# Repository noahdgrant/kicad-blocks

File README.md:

# kicad-blocks

Share schematic sheets across multiple KiCAD projects and reuse their PCB layouts.

`kicad-blocks` is a CLI that lets you treat hierarchical schematic sheets as the source of truth for a section of a board (MCU subsystem, power, etc.) and replay that section's layout across multiple PCB projects. One MCU sheet, many boards — modular dev panels, all-in-one dev boards, space-constrained production boards — without copy-paste or DNP gymnastics.

> Status: pre-alpha. The v0.1 PRD lives at [issue #1](https://github.com/noahdgrant/kicad-blocks/issues/1) and the implementation slices at issues [#2–#13](https://github.com/noahdgrant/kicad-blocks/milestone/1).

## What it does

Given KiCAD projects that share hierarchical schematic sheets (KiCAD 6+ instance-data model), `kicad-blocks` provides four commands:

- **reuse** — copy a sheet's PCB layout (footprint placements, tracks, vias, zones, silkscreen) from a source PCB into a target PCB, anchored at a footprint refdes. Pass `--dry-run` to preview the planned placements without writing.
- **sync** — re-apply after the source layout changes, with a dry-run diff and interactive confirmation.
- **scaffold** — generate a new KiCAD project skeleton wired up to a chosen set of shared sheets.
- **panelize-config** — emit a [KiKit](https://github.com/yaqwsx/KiKit) JSON config to panelize a set of modular PCBs.

After a successful `reuse`, the plugin writes a `<project>.kicad-blocks.lock.json` sidecar next to the config recording the source PCB hash, the applied block hash, the anchor refdes, and the plugin version. **Commit this file to git** — `sync` consults it to detect drift, and shipping it makes diffs reviewable across machines.

Every subcommand also accepts `--format json` for machine-readable output. The JSON envelope is versioned (`schema_version: 1`) and shared by success and failure cases, so a consumer can parse a single stream and branch on the top-level `ok` field. Errors travel as structured entries under `errors[]` on stdout, and exit codes match the default text mode.

## Status

- KiCAD 9 only (uses the modern instance-data schematic model)
- Pure-Python S-expression parsing via [kiutils](https://github.com/mvnmgrx/kiutils)
- MIT licensed

## Install

```sh
pipx install kicad-blocks
```

## Quick start: reuse and sync

Assume you have two KiCAD projects sharing a hierarchical sheet `sheets/mcu.kicad_sch`: a fully-routed `mcu-module/` project that owns the canonical layout, and a `dev-board/` project that wants the same MCU section dropped in.

1. **Scaffold the target project** (skip if you already have one):

   ```sh
   kicad-blocks scaffold --name dev-board --sheets ../sheets/mcu.kicad_sch
   ```

2. **Place the anchor footprint** in `dev-board/dev-board.kicad_pcb` — typically the MCU itself (e.g. `U1`) — at the position and rotation where you want the block to land. Save the board.

3. **Write `dev-board/kicad-blocks.toml`**:

   ```toml
   [[blocks]]
   source   = "../mcu-module/mcu-module.kicad_pcb"
   sheet    = "sheets/mcu.kicad_sch"
   anchor   = "U1"
   ```

4. **Validate the config** before touching the board:

   ```sh
   kicad-blocks validate
   ```

5. **Preview** the planned placement, then apply:

   ```sh
   kicad-blocks reuse --dry-run    # prints the items that would be placed
   kicad-blocks reuse               # writes dev-board.kicad_pcb atomically
   ```

   A `dev-board.kicad-blocks.lock.json` sidecar appears next to your config — commit it.

6. **Later, when the source layout changes**, re-sync:

   ```sh
   kicad-blocks sync --dry-run     # diff: added / removed / moved / net-rewired
   kicad-blocks sync                # prompts before overwriting
   ```

   If `dev-board.kicad_pcb` was hand-edited *inside* the block region since the last apply, `sync` refuses and tells you to pass `--force` once you've reconciled the changes.

For a panel of modular PCBs, declare the `[panelize]` section of `kicad-blocks.toml` and emit a KiKit config with `kicad-blocks panelize-config --out panel.json`, then run KiKit yourself.

## Reporting issues

Bug reports and feature requests welcome at the [issue tracker](https://github.com/noahdgrant/kicad-blocks/issues). Please include the KiCAD version, the `kicad-blocks` version, and a minimal reproducer where possible.

## Contributing

See [CONTRIBUTING.md](./CONTRIBUTING.md) for development setup, the conventional commit format, and how to run the test/lint/typecheck stack locally.

## License

MIT — see [LICENSE](./LICENSE).

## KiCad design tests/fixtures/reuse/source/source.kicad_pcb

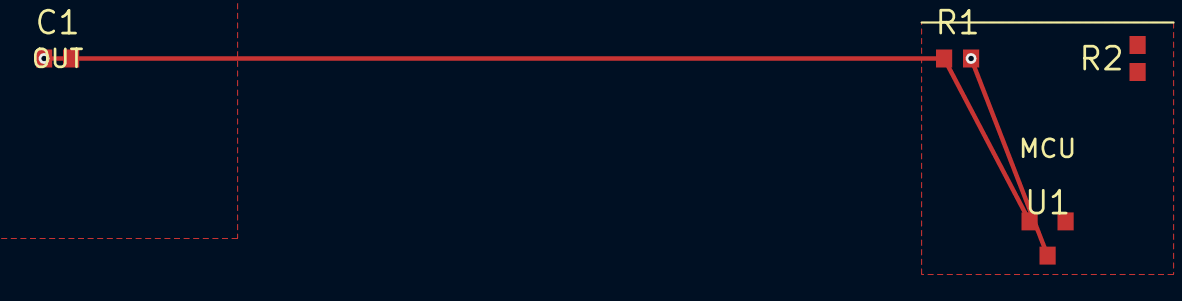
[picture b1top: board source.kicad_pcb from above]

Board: 2 copper layers, 4 parts (0 on the bottom side), 3 nets.

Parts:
C1: 100nF; C_0603_1608Metric
R1, R2: 10k; R_0603_1608Metric
U1: MCU; SOT-23

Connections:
+3V3: C1.1, R1.1, U1.1
GND: C1.2, R2.2, U1.2
SIG: R1.2, R2.1, U1.3

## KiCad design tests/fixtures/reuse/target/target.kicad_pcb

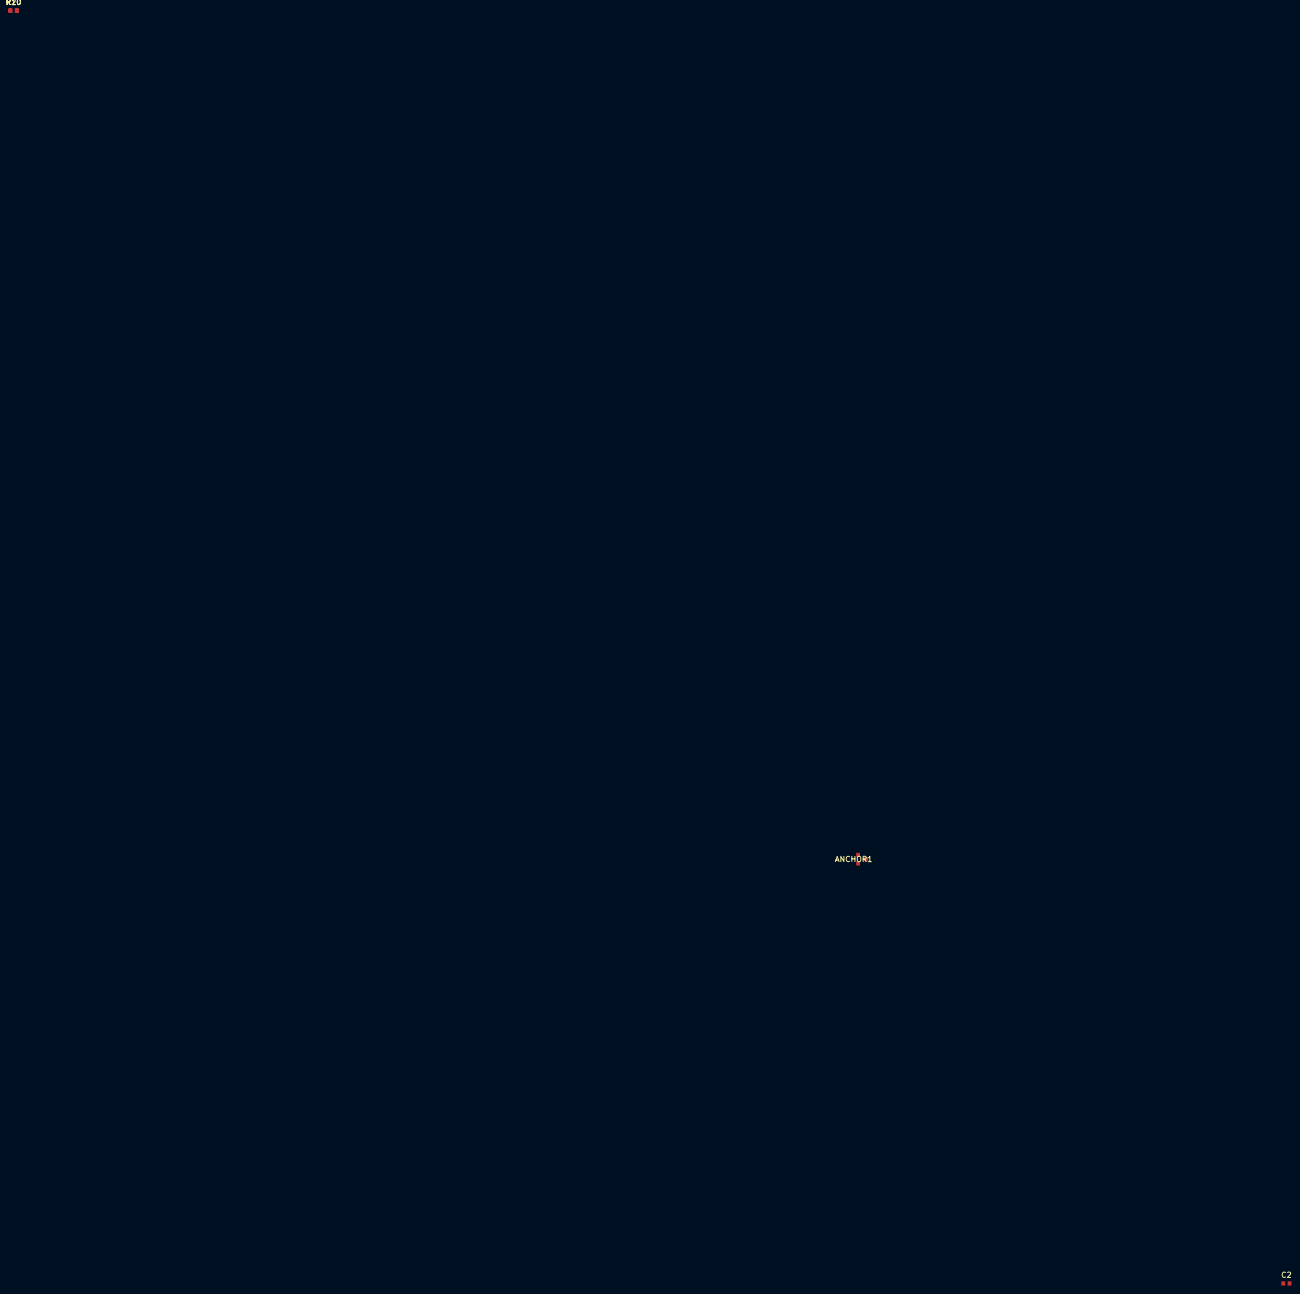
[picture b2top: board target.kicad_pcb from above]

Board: 2 copper layers, 4 parts (0 on the bottom side), 3 nets, no tracks yet.

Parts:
ANCHOR1: MCU; SOT-23
C2: 10uF; C_0603_1608Metric
R10, R20: 10k; R_0603_1608Metric

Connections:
+3V3: ANCHOR1.1, C2.1, R10.1
GND: ANCHOR1.2, C2.2, R20.2
SIG: ANCHOR1.3, R10.2, R20.1

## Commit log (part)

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2026-05-12 chore: bootstrap python package, ci, and conventional commits
    Implements the foundation slice from the v0.1 PRD (#1). Stands up an
    uv-managed Python package with a Click-based CLI, a CI workflow that
    runs ruff + pyright + pytest, a PR-title validation workflow for
    conventional commits, and CONTRIBUTING docs. Removes PRD.md
    (canonical PRD lives at issue #1).
    Key decisions:
2026-05-12 chore: adopt strict ruff config from prevasum/backend
    Replaces the moderate default ruleset with the canonical config from
    prevasum/backend (Noah's baseline). Adds D1 docstrings, ANN type
    annotations, T20 no-print, DOC/DTZ/TRY rules, and others. Adapted
    for kicad-blocks:
    - target-version pinned to py311 (matches requires-python)
    - dropped fastapi-specific bugbear extension
2026-05-12 ci: surface import-order check as its own step
    Splits the import-order subset (ruff `I` rule) into a dedicated
    labeled step so a violation shows up as its own CI failure rather
    than buried in the omnibus `ruff check` output. The rule is already
    in `[tool.ruff.lint].select`, so this adds visibility, not new
    coverage. Also adds the explicit `.` path arg to ruff invocations to
    match prevasum/backend's convention.
2026-05-12 ci: remove redundant import-order step
    The `I` (isort) rule is already in `[tool.ruff.lint].select`, so
    `ruff check` covers import order. The dedicated step added in the
    previous commit was redundant.
    Refs: #2
    Authored by: RALPH
2026-05-12 refactor: read version from package metadata at the use site
    Removes `__version__` from `__init__.py` entirely. `cli.py` and the
    test now call `importlib.metadata.version("kicad-blocks")` directly.
    pyproject.toml stays the single source of truth — release-please will
    update it, and there's no re-export layer to drift.
    Refs: #2
    Authored by: RALPH
2026-05-12 chore: bootstrap python package, ci, and conventional commits (#14)
    Implements the foundation slice from the v0.1 PRD (#1). Stands up an
    uv-managed Python package with a Click-based CLI, a CI workflow that
    runs ruff + pyright + pytest, a PR-title validation workflow for
    conventional commits, and CONTRIBUTING docs. Removes PRD.md
    (canonical PRD lives at issue #1).
    Key decisions:
2026-05-12 feat: add validate and list-block subcommands (Slice 2 read-path tracer)
    PRD reference: #1 (Slice 2 — issue #3). Adds the read-side of the plugin
    end-to-end: kicad_io (kiutils-backed typed footprint model), config (TOML
    loader with file/line-aware errors), block.footprints_in_sheet (sheet
    membership query), reporter, and validate + list-block CLI subcommands.
    A synthetic minimal fixture is committed under tests/fixtures/minimal/.
    Key decisions:
2026-05-12 feat: add validate and list-block subcommands (Slice 2 read-path tracer) (#15)
    PRD reference: #1 (Slice 2 — issue #3). Adds the read-side of the plugin
    end-to-end: kicad_io (kiutils-backed typed footprint model), config
    (TOML loader with file/line-aware errors), block.footprints_in_sheet (sheet
    membership query), reporter, and validate + list-block CLI subcommands.
    A synthetic minimal fixture is committed under tests/fixtures/minimal/.
    Key decisions:
2026-05-12 feat(reuse): add write-path tracer for footprint placement (Slice 3)
    Implements the footprint-only half of `kicad-blocks reuse` end-to-end: a pure
    `transform` module for 2D affine math, a `block.plan_apply` planner that pairs
    source and target footprints by symbol UUID and computes anchor-relative
    placements, and an atomic apply helper in `kicad_io` that writes via temp +
    `os.replace`. CLI gains `reuse --dry-run` and the apply path.
    Net mapping is a Slice-3 stub per PRD #1: any source net missing from the
2026-05-12 feat(reuse): add write-path tracer for footprint placement (Slice 3) (#16)
    Implements the footprint-only half of `kicad-blocks reuse` end-to-end: a
    pure
    `transform` module for 2D affine math, a `block.plan_apply` planner that
    pairs
    source and target footprints by symbol UUID and computes anchor-relative
    placements, and an atomic apply helper in `kicad_io` that writes via
2026-05-12 feat(net-map): auto-match nets with per-block overrides (Slice 4)
    Adds the ``net_map`` module that resolves source-block net names against the
    target PCB's net list. Identical names auto-match (with leading slashes in
    hierarchical net paths normalized so ``/PWR/+3V3`` and ``PWR/+3V3`` are the
    same net). Names that diverge between projects are resolved by an explicit
    ``[blocks.<name>.net_map]`` override table. Unresolved nets ride on the
    :class:`ApplyPlan`; ``reuse --dry-run`` prints them as warnings, the actual
2026-05-12 feat(net-map): auto-match nets with per-block overrides (Slice 4) (#17)
    Adds the ``net_map`` module that resolves source-block net names against
    the
    target PCB's net list. Identical names auto-match (with leading slashes
    in
    hierarchical net paths normalized so ``/PWR/+3V3`` and ``PWR/+3V3`` are
    the
2026-05-12 feat(reuse): copy in-block tracks and vias (Slice 5)
    Carries the routing half of the reuse pipeline through plan_apply and
    the kicad_io write path so the source PCB's tracks and vias for a block
    land in the target at the anchor-relative transform, with net names
    rewritten through the per-block net_map. Boundary-crossing items are
    surfaced on the plan's excluded_* lists so dry-run shows what's not
    coming with. PRD slice 5 of issue #1.
2026-05-12 feat(reuse): copy in-block tracks and vias (Slice 5) (#18)
    Carries the routing half of the reuse pipeline through plan_apply and
    the kicad_io write path so the source PCB's tracks and vias for a block
    land in the target at the anchor-relative transform, with net names
    rewritten through the per-block net_map. Boundary-crossing items are
    surfaced on the plan's excluded_* lists so dry-run shows what's not
    coming with. PRD slice 5 of issue #1.
2026-05-12 style: apply ruff format to slice 6 changes
    CI flagged 4 files as unformatted; this is a pure-whitespace pass with no
    semantic changes. Lint, pyright, and pytest still clean locally.
    Authored by: RALPH
    Closes: #7
2026-05-12 feat(reuse): copy zones, board graphics, and check layer stackup (Slice 6) (#19)
    Closes the reuse scope from PRD #1: copper zones and board-level
    silkscreen/fab/courtyard graphics now travel with a block, filtered by a
    padded AABB hull around the in-block footprint pads. Source/target layer
    stackups are compared up front; mismatches raise ApplyError unless the
    block opts in via `allow_layer_mismatch = true`. Cached zone fills are
    dropped on copy so KiCAD repours on the target.
2026-05-12 feat(sync): add sync --dry-run, BlockDiff, and lock JSON sidecar (Slice 7)
    Introduces the read side of the sync workflow per PRD #1:
    - New `sync_state` module reads/writes `<project>.kicad-blocks.lock.json`
    with `schema_version`, per-block source PCB hash, applied block hash,
    anchor refdes, sheet path, and plugin version. Provides `hash_file`
    and `hash_applied_block` so the lock can be produced from a plan.
    - New `diff` module computes a structured `BlockDiff` between the source
2026-05-12 style: apply ruff format to slice 7 files
    Authored by: RALPH
    Closes: #8
2026-05-12 feat(sync): add sync --dry-run, BlockDiff, and lock JSON sidecar (Slice 7) (#20)
    Introduces the read side of the sync workflow per PRD #1:
    - New `sync_state` module reads/writes
    `<project>.kicad-blocks.lock.json`
    with `schema_version`, per-block source PCB hash, applied block hash,
    anchor refdes, sheet path, and plugin version. Provides `hash_file`
    and `hash_applied_block` so the lock can be produced from a plan.
2026-05-12 feat(sync): sync apply with hand-edit conflict detection (Slice 8)
    Implements the apply path for ``kicad-blocks sync`` per PRD #1, Slice 8 (#9).
    - ``sync`` (no flags) computes the diff, hashes the target's current block
    region, and aborts with a clear conflict message when that hash diverges
    from the lock's ``applied_block_hash``. Without a conflict it prompts
    y/N and applies on confirmation, refreshing the lock on success.
    - ``sync --force`` skips the prompt and overrides conflicts.
2026-05-13 feat(sync): sync apply with hand-edit conflict detection (Slice 8) (#21)
    Implements the apply path for ``kicad-blocks sync`` per PRD #1, Slice 8
    (#9).
    - ``sync`` (no flags) computes the diff, hashes the target's current
    block
    region, and aborts with a clear conflict message when that hash diverges
    from the lock's ``applied_block_hash``. Without a conflict it prompts
2026-05-13 feat(scaffold): add scaffold command for new KiCAD projects (Slice 9)
    Implements the `scaffold` subcommand from PRD #1. Generates a new
    project directory containing a minimal `.kicad_pro`, a root
    `.kicad_sch` with hierarchical sheet refs, an empty `.kicad_pcb`
    with a placeholder rectangle on `Edge.Cuts`, and a starter
    `kicad-blocks.toml` listing the chosen sheets.
    Key decisions:
2026-05-13 style(scaffold): apply ruff format
    Authored by: RALPH
2026-05-13 feat(scaffold): add scaffold command for new KiCAD projects (Slice 9) (#22)
    Implements the `scaffold` subcommand from PRD #1. Generates a new
    project directory containing a minimal `.kicad_pro`, a root
    `.kicad_sch` with hierarchical sheet refs, an empty `.kicad_pcb`
    with a placeholder rectangle on `Edge.Cuts`, and a starter
    `kicad-blocks.toml` listing the chosen sheets.
    Key decisions:
2026-05-13 feat(panelize): add panelize-config command emitting KiKit JSON preset (Slice 10)
    Implements Slice 10 from the v0.1 PRD (issue #1): a new
    `panelize-config` subcommand that translates the `[panelize]` section
    of `kicad-blocks.toml` into a KiKit-compatible JSON preset. We deliberately
    do not invoke KiKit ourselves so the project isn't pinned to a particular
    KiKit release.
    Key decisions:
2026-05-13 feat(panelize): add panelize-config command emitting KiKit JSON preset (Slice 10) (#23)
    Implements Slice 10 from the v0.1 PRD (issue #1): a new
    `panelize-config` subcommand that translates the `[panelize]` section
    of `kicad-blocks.toml` into a KiKit-compatible JSON preset. We
    deliberately
    do not invoke KiKit ourselves so the project isn't pinned to a
    particular
2026-05-13 feat(cli): add --format json across all commands (Slice 11)
    Implements parent PRD #1, Slice 11: every subcommand (validate, list-block,
    reuse, sync, scaffold, panelize-config) accepts `--format {text,json}` and
    defaults to text. JSON mode emits a single versioned envelope on stdout —
    `{"schema_version": 1, "command": ..., "ok": bool, ...}` — with errors
    surfaced as structured entries under `errors[]`. Exit codes are unchanged.
    Key decisions:
2026-05-13 feat(cli): add --format json across all commands (Slice 11) (#24)
    Implements parent PRD #1, Slice 11: every subcommand (validate,
    list-block,
    reuse, sync, scaffold, panelize-config) accepts `--format {text,json}`
    and
    defaults to text. JSON mode emits a single versioned envelope on stdout
    —
2026-05-13 feat(release): wire release-please + OIDC PyPI publishing (Slice 12) (#25)
    Adds the tag-driven release pipeline described in PRD #1 / Slice 12 (#13):
    - release-please-config.json + .release-please-manifest.json track the
    kicad-blocks Python package and seed the manifest at the current
    pyproject version (0.0.0).
    - .github/workflows/release-please.yml maintains the release PR on every
    push to main via googleapis/release-please-action@v4. Merging the PR
